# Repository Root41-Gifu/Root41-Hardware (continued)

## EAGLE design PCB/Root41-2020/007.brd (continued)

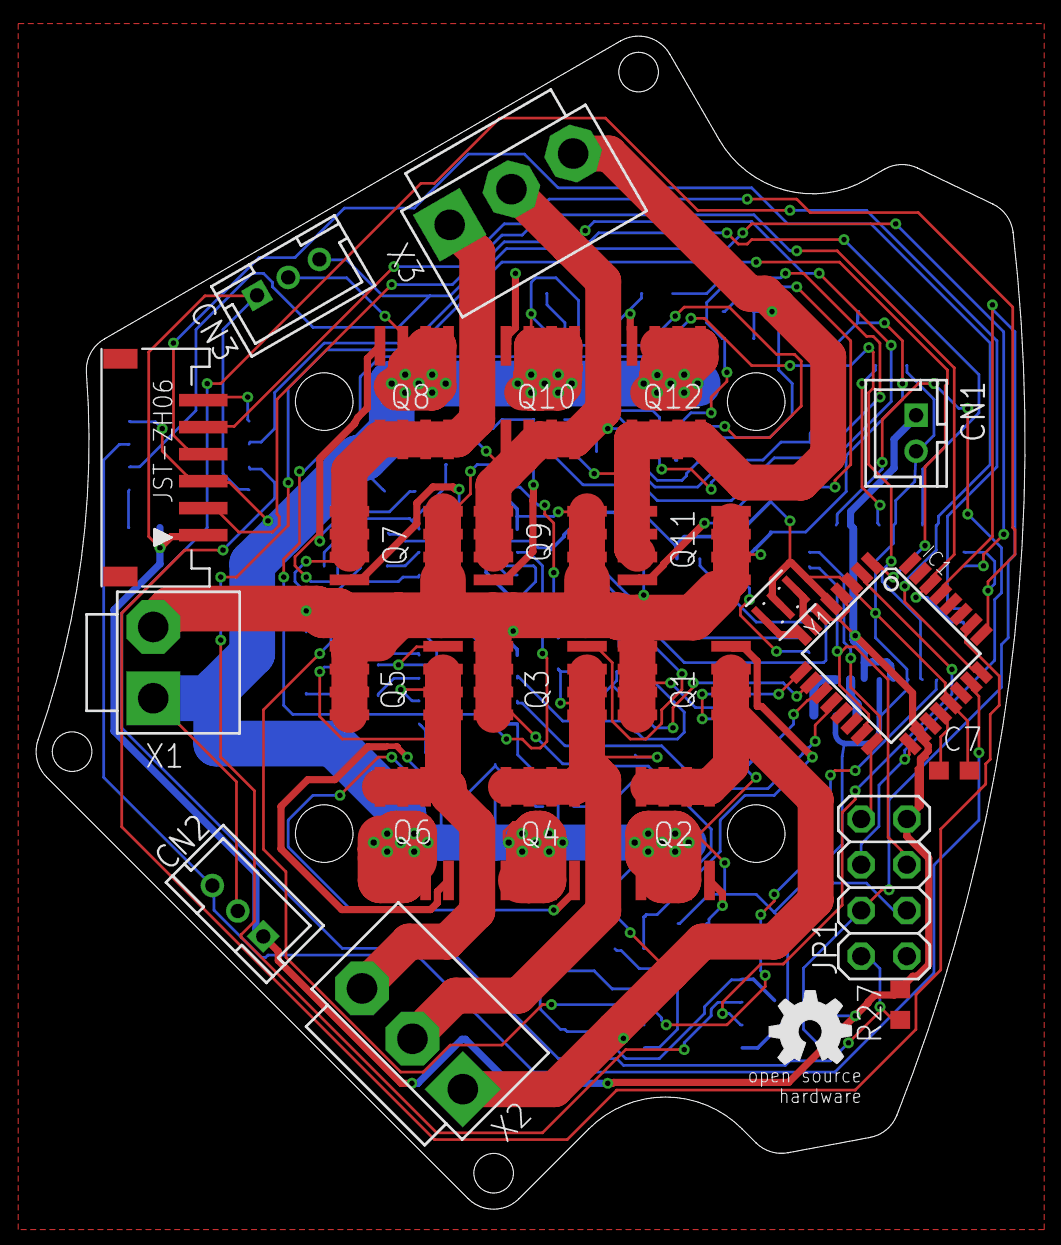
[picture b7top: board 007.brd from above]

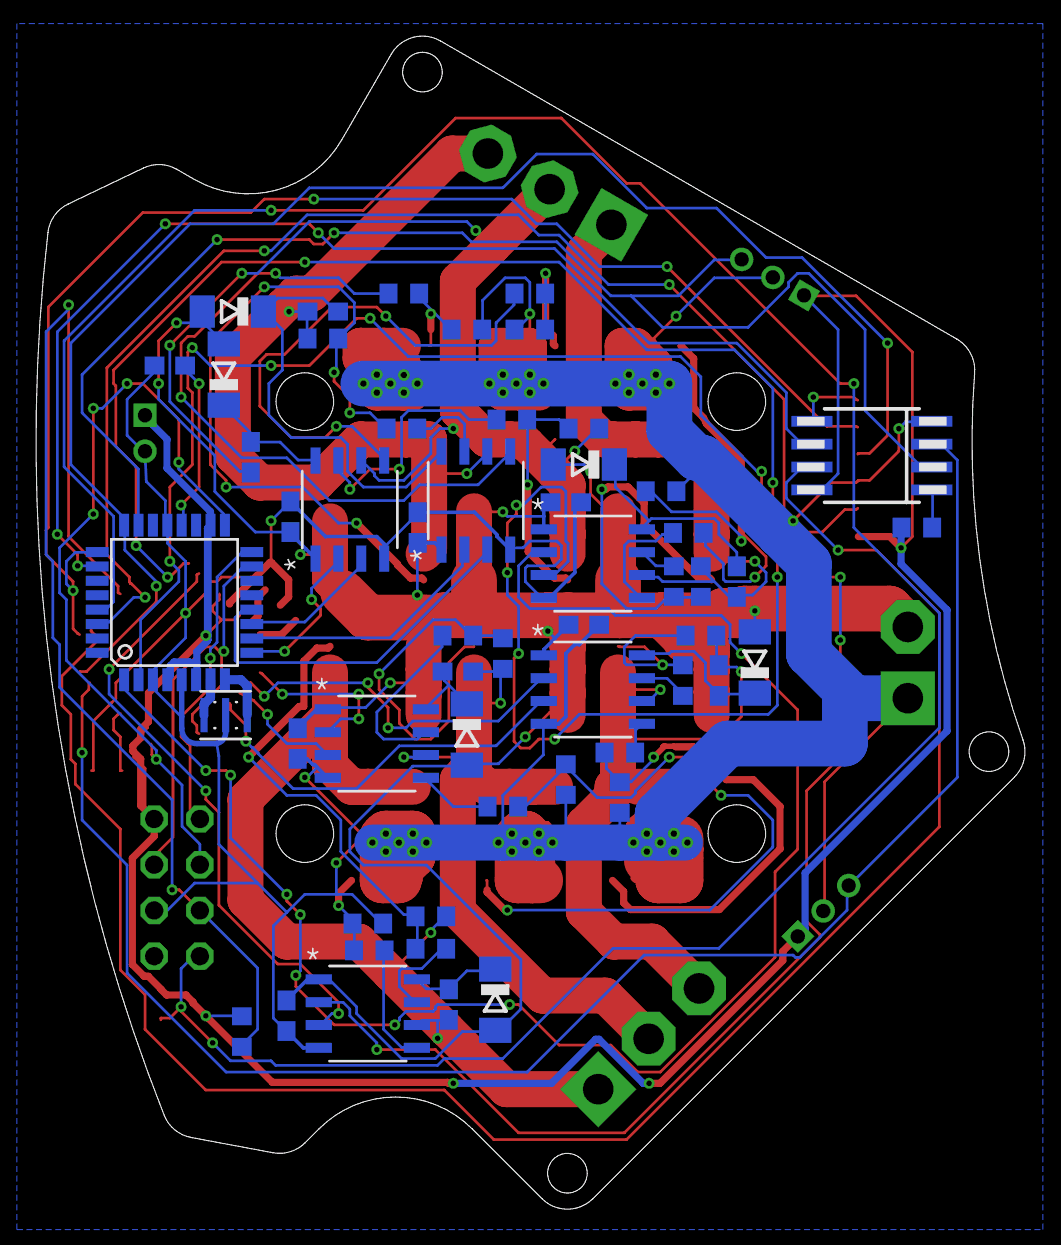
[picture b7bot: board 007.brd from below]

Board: 2 copper layers, 54.9 x 65.2 mm, 79 parts (54 on the bottom side), 71 nets.

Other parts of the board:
U$1: OSHW_5MM

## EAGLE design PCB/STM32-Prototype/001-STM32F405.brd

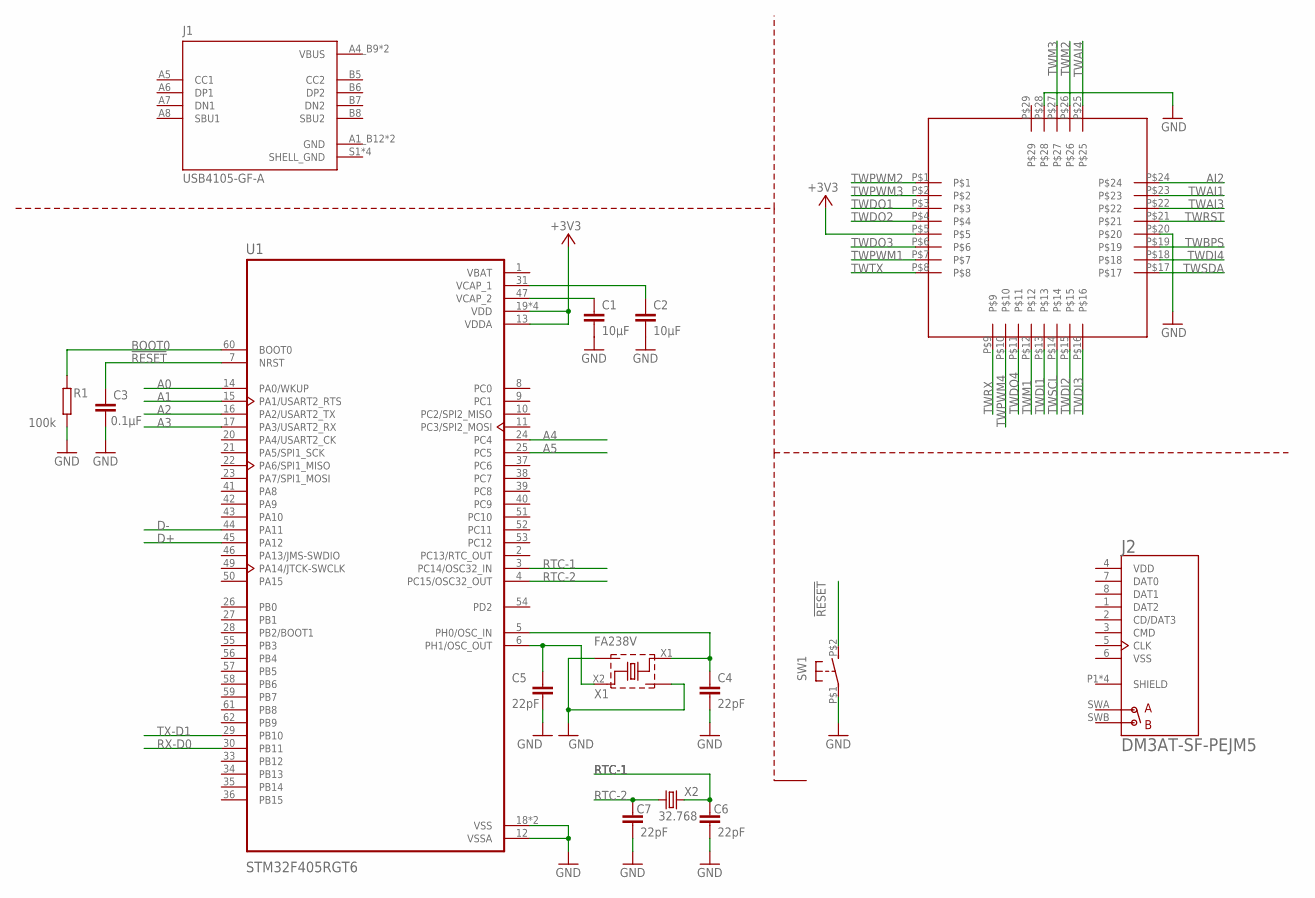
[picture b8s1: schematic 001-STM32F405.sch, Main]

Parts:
C1, C2: 10μF; C1608
C3: 0.1μF; C1608
C4, C5, C6, C7: 22pF; C1608
J1: USB4105-GF-A; GCT_USB4105-GF-A
J2: DM3AT-SF-PEJM5; HRS_DM3AT-SF-PEJM5
R1: 100k; SMD1608
SW1: TVAF06-A020B-R
U1: STM32F405RGT6; QFP50P1200X1200X160-64N
U$1: LITE
X1: FA238V
X2: 32.768; FC-135

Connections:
!RESET: C3.1, SW1.P$2 (S), U1.7 (NRST)
+3V3: U1.13 (VDDA), U1.19 (VDD), U1.32 (VDD), U1.48 (VDD), U1.64 (VDD), U$1.P$5
A0: U1.14 (PA0/WKUP)
A1: U1.15 (PA1/USART2_RTS)
A2: U1.16 (PA2/USART2_TX)
A3: U1.17 (PA3/USART2_RX)
A4: U1.24 (PC4)
A5: U1.25 (PC5)
AI2: U$1.P$24
BOOT0: R1.1, U1.60 (BOOT0)
D+: U1.45 (PA12)
D-: U1.44 (PA11)
GND: C1.2, C2.2, C3.2, C4.2, C5.2, C6.2, C7.2, J1.A1_B12 (GND), J1.B1_A12 (GND), R1.2, SW1.P$1, U1.12 (VSSA), U1.18 (VSS), U1.63 (VSS), U$1.P$20, U$1.P$28, X1.GND, X1.GND2 (GND1)
unnamed: C1.1, U1.47 (VCAP_2)
unnamed: C2.1, U1.31 (VCAP_1)
unnamed: C4.1, U1.5 (PH0/OSC_IN), X1.X1 (1)
unnamed: C5.1, U1.6 (PH1/OSC_OUT), X1.X2 (2)
RTC-1: C6.1, U1.3 (PC14/OSC32_IN), X2.P$2 (2)
RTC-2: C7.1, U1.4 (PC15/OSC32_OUT), X2.P$1 (1)
RX-D0: U1.30 (PB11)
SHELL_GND: J1.S1 (SHELL_GND), J1.S2 (SHELL_GND), J1.S3 (SHELL_GND), J1.S4 (SHELL_GND)
TWAI1: U$1.P$23
TWAI3: U$1.P$22
TWAI4: U$1.P$25
TWBPS: U$1.P$19
TWDI1: U$1.P$13
TWDI2: U$1.P$15
TWDI3: U$1.P$16
TWDI4: U$1.P$18
TWDO1: U$1.P$3
TWDO2: U$1.P$4
TWDO3: U$1.P$6
TWDO4: U$1.P$11
TWM1: U$1.P$12
TWM2: U$1.P$26
TWM3: U$1.P$27
TWPWM1: U$1.P$7
TWPWM2: U$1.P$1
TWPWM3: U$1.P$2
TWPWM4: U$1.P$10
TWRST: U$1.P$21
TWRX: U$1.P$9
TWSCL: U$1.P$14
TWSDA: U$1.P$17
TWTX: U$1.P$8
TX-D1: U1.29 (PB10)
VBAT: U1.1 (VBAT)
VBUS: J1.A4_B9 (VBUS), J1.B4_A9 (VBUS)
VDD: J2.4 (VDD)
VSS: J2.6 (VSS)

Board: 2 copper layers, 15 parts (0 on the bottom side), 12 nets, no tracks yet.

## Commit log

2021-02-22 ライセンス表記の名前をRoot41に変更
2021-02-23 Eagleのプロジェクトファイル及びプロジェクトフォルダを作成。
2021-02-23 001-CPU Boardの回路図と基板ファイルを作成。
2021-03-04 評価ボードの回路図の大枠
2021-03-05 リポジトリのロゴ画像を追加
2021-03-07 重量目標を追加
2021-03-08 3D設計のリンクを記載
2021-08-09 no message
2021-08-17 ラインセンサできた
2021-08-19 部品配置中
2021-08-19 配置完了！
2021-08-21 もうどうにでもなれ
2021-08-25 ボールセンサ配置完了
2021-08-28 睡眠不足はいい仕事の敵だ
2021-08-28 てめぇなんかにフィオをやれるか！
2021-08-28 ひとまず配線終わったのだ！疲れたのだ！あとは電源基板とエンコーダ基板だけなのだ！
2021-08-28 コミットし忘れてたのだ！
2021-09-27 基板設計完了
2021-10-24 DRV8332ESC設計した
